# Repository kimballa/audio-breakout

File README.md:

Breadboard audio breakout
=========================

This board is intended to sit next to a pair of breadboards and plug into the power bus rows and the
first few columns of each breadboard. Measurements were taken on Adafruit breadboards.

Power
-----

Power bus rows are filled with +12V, GND, and -12V from the onboard power header.
* This takes a molex 3-pin MicroFit 3.0 cable from a GS-101-PWR.
* There is a power switch, and LEDs to show you when it's engaged.
* There are jumper headers that the power flows through before accessing your board.
  * Close these with SPC02SYAN shunt jumpers to let the power flow.
  * Or hook your ammeter here to measure current consumption precisely.
  * The onboard opamp and LEDs are upstream of the jumpers and will not be included 
    in your current measurements.
* There is also a 3-pin MicroFit 3.0 header to daisy-chain a cable to a module under test,
  for current measurement purposes.

Leveling feet
-------------

The two mounting holes on the outboard edge of the PCB are sized for an M3 screw. A 20mm machine
screw with an integral end-stop like JLCPCB Mechatronics' EKLF-W-P12-M3-L20 can be used to balance
this edge of the board so that it lies flat when you adjust potentiometers or plug in cables.

Reference voltages
-------------------

There are two reference voltages generated onboard and brought out to pins, at 8.0V and 6.0V. Use
the two trimpots on the bottom of the PCB to calibrate these.

Jacks
-----

There are six jacks, `IO1..IO4`, `OUT1`, and `OUT2`. 

The I/O jacks are general purpose and bidirectional. Shields are attached to GND via 1M resistance.
The tip goes to the labeled pin on the breadboard.

OUT1 and OUT2 are unity buffered by an opamp with 220kOhm input impedence. These are intended to
drive a signal to a speaker or other external system. The TL074H opamp is specified to deliver at
least 25mA before losing voltage fidelity. The shields for OUT1 and OUT2 are directly connected to
GND. 

There are also header pins on the top of the board for accessing OUT1 and OUT2 on a 'scope or
multimeter.

Pots
----

There are four PTV09 potentiometers, two at 100kOhm and two at 10kOhm resistance. All three pins of
each pot are brought out to the breadboard. Pin numbers are indicated with one to three dots.

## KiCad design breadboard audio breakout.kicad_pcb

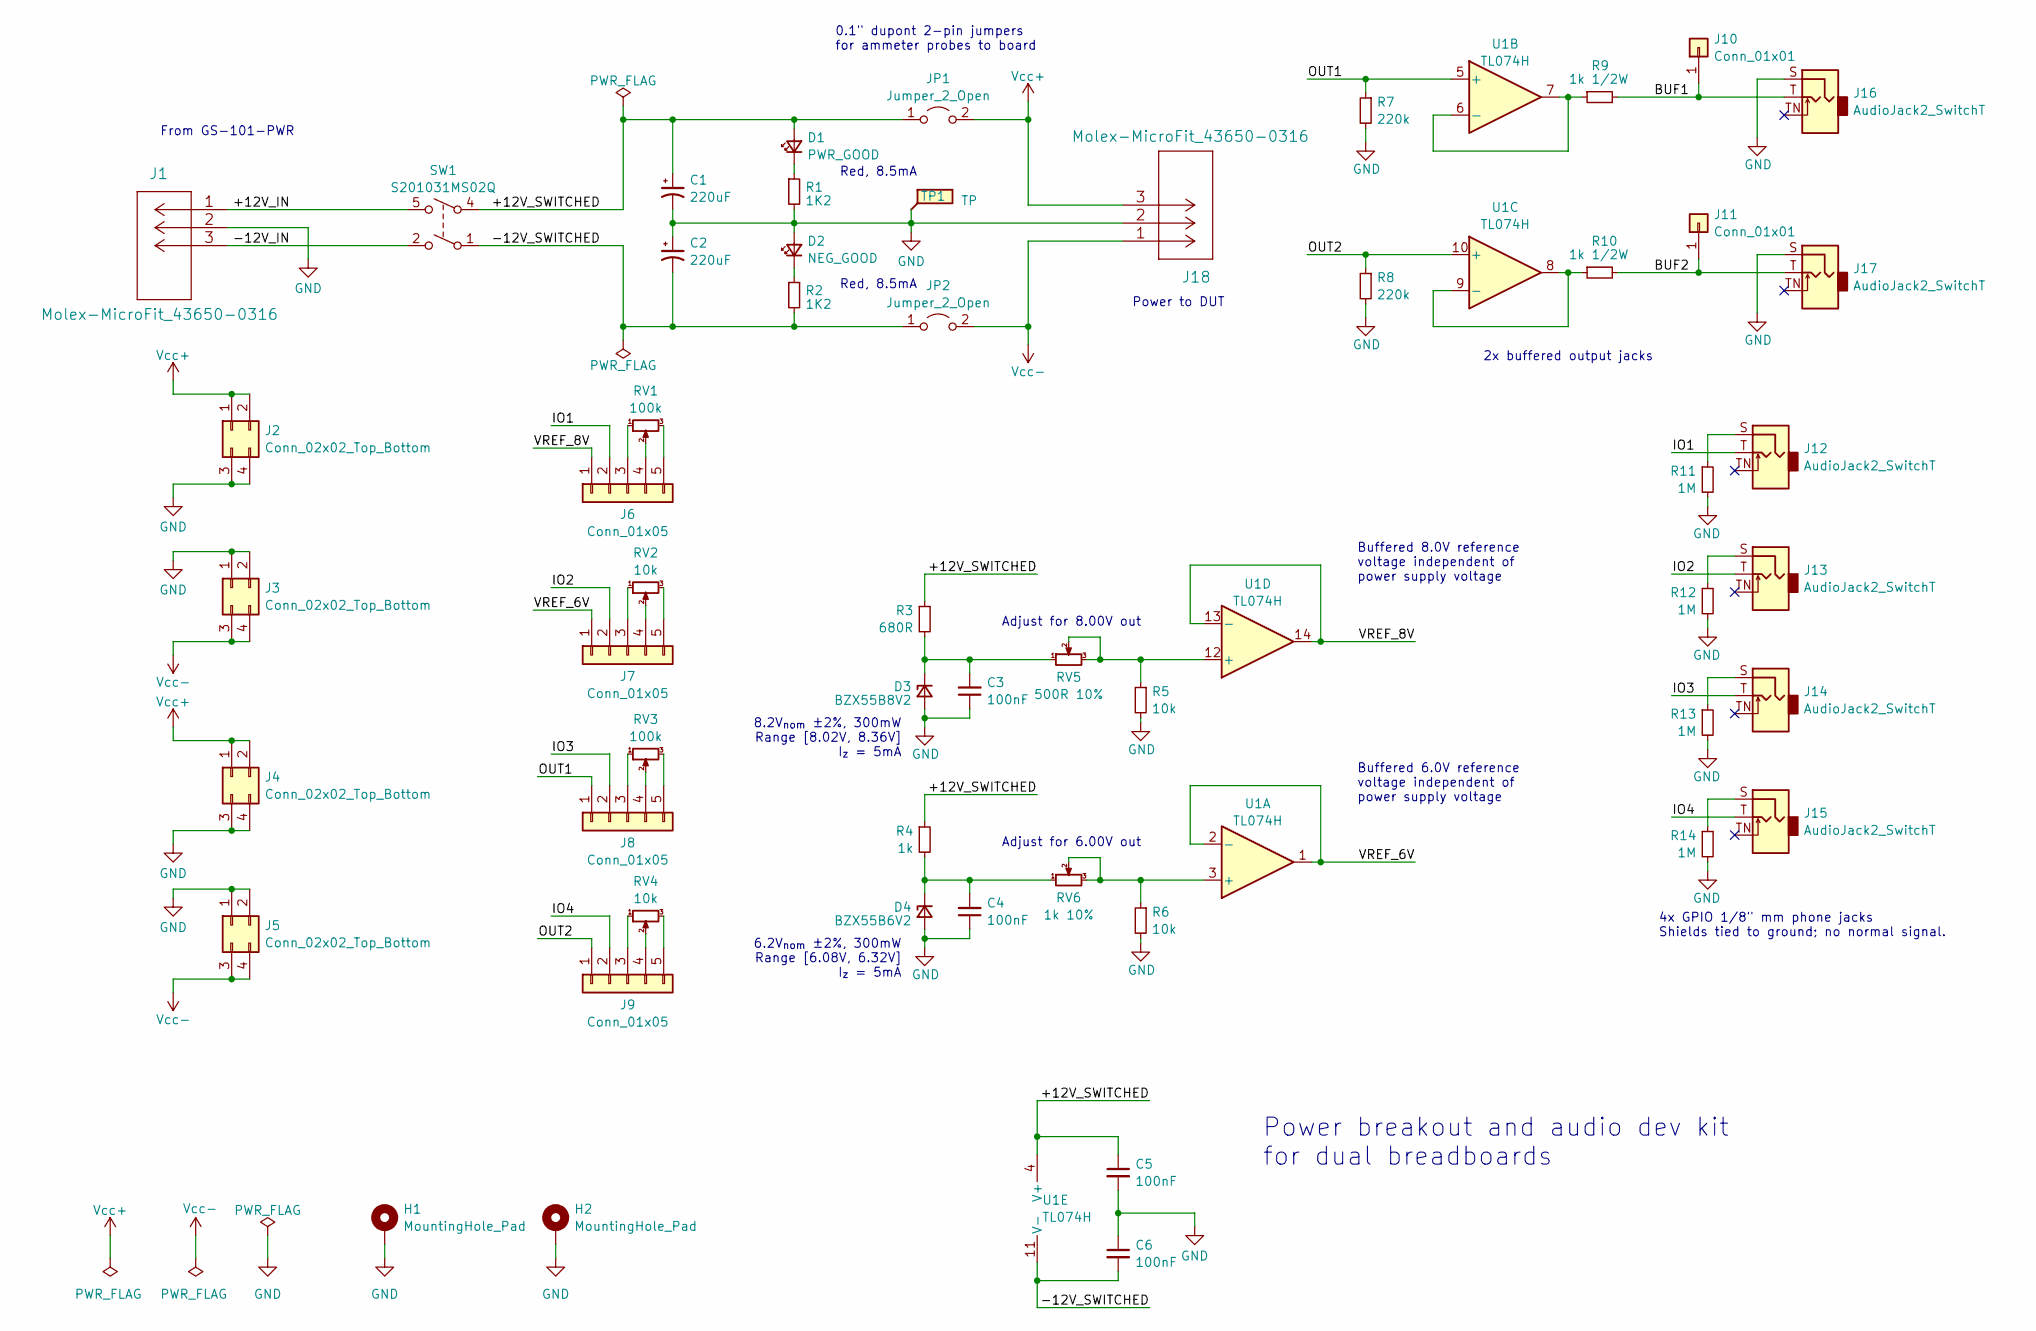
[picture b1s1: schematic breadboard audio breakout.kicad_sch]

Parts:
C1, C2: 220uF; CP_Radial_D10.0mm_P5.00mm; MPN ESW227M035AH9AA
C3, C4, C5, C6: 100nF; C_0805_2012Metric_Pad1.18x1.45mm_HandSolder; MPN CL21B104KBFNNNE
D1: PWR_GOOD; LED_D5.0mm_SilkFix; MPN LTL-4223
D2: NEG_GOOD; LED_D5.0mm_SilkFix; MPN LTL-4223
D3: BZX55B8V2; D_SOD-323_HandSoldering; MPN MM3Z8V2ST1G
D4: BZX55B6V2; D_SOD-323_HandSoldering; MPN MM3Z6V2ST1G
H1, H2: MountingHole_Pad; MountingHole_3.3mm_M3_Full_Standoff_Size
J1, J18: Molex-MicroFit_43650-0316; Molex-Microfit-43650-0316; MPN 436500316
J2, J3, J4, J5: Conn_02x02_Top_Bottom; PinHeader_2x02_P2.54mm_Vertical; MPN 67997-400HLF
J6, J7, J8, J9: Conn_01x05; PinHeader_1x05_P2.54mm_Vertical; MPN 5-146850-1
J10, J11: Conn_01x01; PinHeader_1x01_P2.54mm_Vertical; MPN 5-146850-1
J12, J13, J14, J15, J16, J17: AudioJack2_SwitchT; Schurter-4832.2211; MPN 4832.2211
JP1, JP2: Jumper_2_Open; PinHeader_1x02_P2.54mm_Vertical; MPN 5-146850-1
R1, R2: 1K2; R_0805_2012Metric_Pad1.20x1.40mm_HandSolder; MPN RMCF0805FT1K20
R3: 680R; R_0805_2012Metric_Pad1.20x1.40mm_HandSolder; MPN RMCF0805FT680R
R4: 1k; R_0805_2012Metric_Pad1.20x1.40mm_HandSolder; MPN RMCF0805FT1K00
R5, R6: 10k; R_0805_2012Metric_Pad1.20x1.40mm_HandSolder; MPN RMCF0805FT10K0
R7, R8: 220k; R_0805_2012Metric_Pad1.20x1.40mm_HandSolder; MPN RMCF0805FT220K
R9, R10: 1k 1/2W; R_1206_3216Metric_Pad1.30x1.75mm_HandSolder; MPN RNCP1206FTD1K00
R11, R12, R13, R14: 1M; R_0805_2012Metric_Pad1.20x1.40mm_HandSolder; MPN RMCF0805FT1M00
RV1, RV3: 100k; Pot_Bourns_PTV09_vert_3dModel; MPN PTV09A-4025F-B104
RV2, RV4: 10k; Pot_Bourns_PTV09_vert_3dModel; MPN PTV09A-4025F-B103
RV5: 500R 10%; Pot_Bourns_3362P; MPN 3362P-1-501LF
RV6: 1k 10%; Pot_Bourns_3362P; MPN 3362P-1-102LF
SW1: S201031MS02Q; CK_SPDT_S201031MS02Q; MPN S201031MS02Q
TP1: TP; TP_HeaderPin_P2.54mm_round
U1: TL074H; TI_SOIC_D_R-PDSO-G14; MPN TL074HIDR

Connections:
/+12V_IN: J1.1, SW1.5
/+12V_SWITCHED: C1.1, C5.1, D1.2 (A), JP1.1 (A), R3.1, R4.1, SW1.4, U1.4 (V+)
/-12V_IN: J1.3, SW1.2
/-12V_SWITCHED: C2.2, C6.2, JP2.1 (A), R2.2, SW1.1, U1.11 (V-)
/BUF1: J10.1, J16.T, R9.2
/BUF2: J11.1, J17.T, R10.2
/IO1: J6.2, J12.T
/IO2: J7.2, J13.T
/IO3: J8.2, J14.T
/IO4: J9.2, J15.T
/OUT1: J8.1, R7.1, U1.5 (+)
/OUT2: J9.1, R8.1, U1.10 (+)
/VREF_6V: J7.1, U1.1, U1.2 (-)
/VREF_8V: J6.1, U1.13 (-), U1.14
GND: C1.2, C2.1, C3.1, C4.1, C5.2, C6.1, D2.2 (A), D3.2 (A), D4.2 (A), H1.1, H2.1, J1.2, J2.3, J2.4, J3.1, J3.2, J4.3, J4.4, J5.1, J5.2, J16.S, J17.S, J18.2, R1.2, R5.2, R6.2, R7.2, R8.2, R11.2, R12.2, R13.2, R14.2, TP1.1
unnamed: D1.1 (K), R1.1
unnamed: D2.1 (K), R2.1
unnamed: C3.2, D3.1 (K), R3.2, RV5.1
unnamed: C4.2, D4.1 (K), R4.2, RV6.1
unnamed: J6.3, RV1.1
unnamed: J6.4, RV1.2
unnamed: J6.5, RV1.3
unnamed: J7.3, RV2.1
unnamed: J7.4, RV2.2
unnamed: J7.5, RV2.3
unnamed: J8.3, RV3.1
unnamed: J8.4, RV3.2
unnamed: J8.5, RV3.3
unnamed: J9.3, RV4.1
unnamed: J9.4, RV4.2
unnamed: J9.5, RV4.3
unnamed: J12.S, R11.1
unnamed: J13.S, R12.1
unnamed: J14.S, R13.1
unnamed: J15.S, R14.1
unnamed: R6.1, RV6.2, RV6.3, U1.3 (+)
unnamed: R9.1, U1.6 (-), U1.7
unnamed: R10.1, U1.8, U1.9 (-)
unnamed: R5.1, RV5.2, RV5.3, U1.12 (+)
Vcc+: J2.1, J2.2, J4.1, J4.2, J18.3, JP1.2 (B)
Vcc-: J3.3, J3.4, J5.3, J5.4, J18.1, JP2.2 (B)

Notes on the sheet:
8.2V_{nom} ±2%, 300mW Range [8.02V, 8.36V] I_{z} = 5mA
0.1" dupont 2-pin jumpers for ammeter probes to board
Buffered 8.0V reference voltage independent of power supply voltage
6.2V_{nom} ±2%, 300mW Range [6.08V, 6.32V] I_{z} = 5mA
Adjust for 6.00V out
Red, 8.5mA
Power breakout and audio dev kit for dual breadboards
2x buffered output jacks
From GS-101-PWR
Buffered 6.0V reference voltage independent of power supply voltage
4x GPIO 1/8" mm phone jacks Shields tied to ground; no normal signal.
Power to DUT
Adjust for 8.00V out

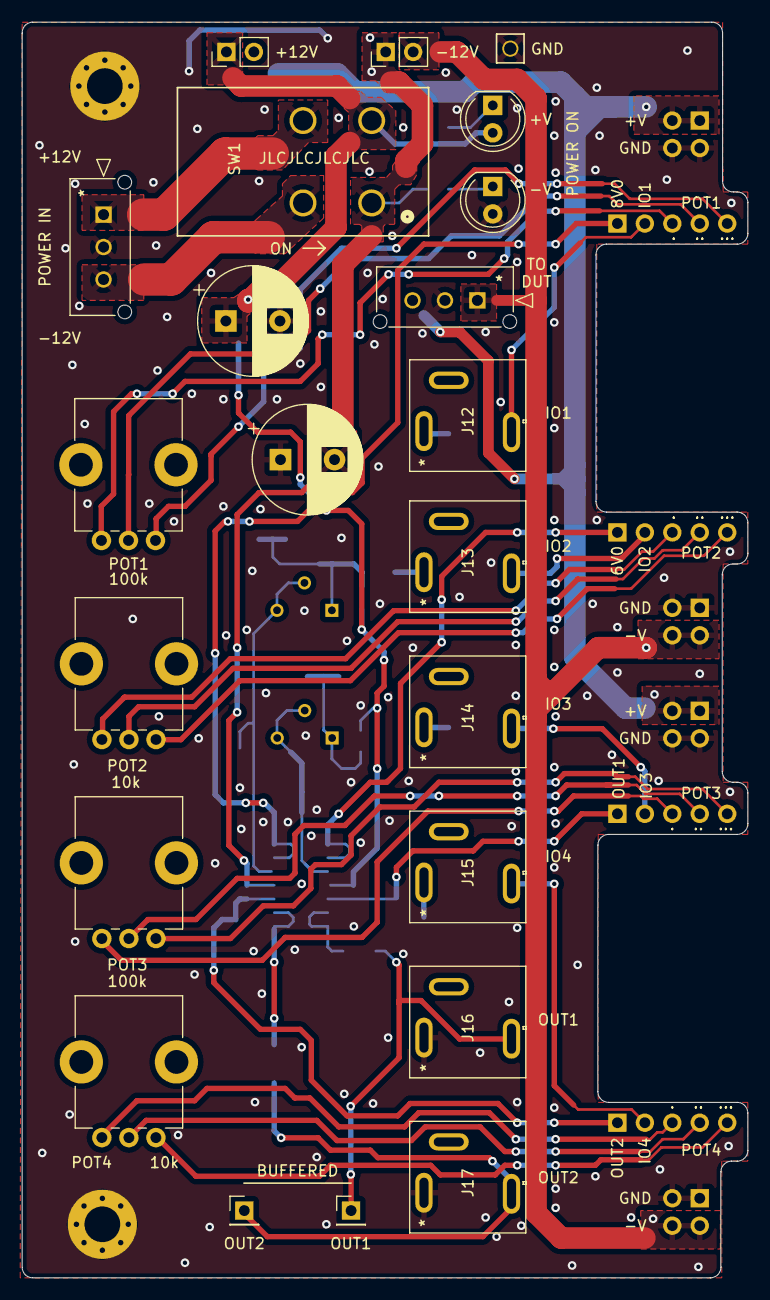
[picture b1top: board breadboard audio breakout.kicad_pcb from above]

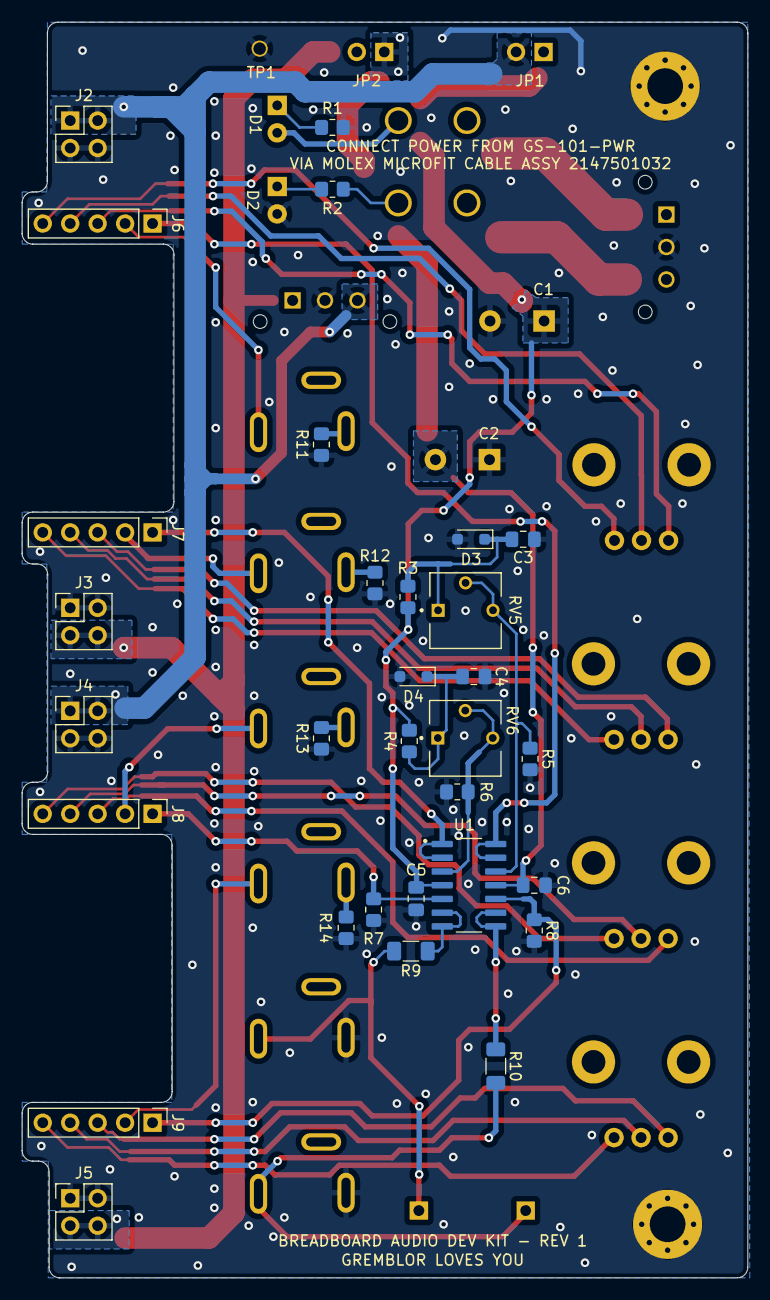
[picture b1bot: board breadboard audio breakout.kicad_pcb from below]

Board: 2 copper layers, 67.1 x 116.2 mm, 55 parts (31 on the bottom side), 41 nets.

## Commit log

2023-12-29 Add gitignore file.
2023-12-29 Add README.
2023-12-29 Add project files.
2023-12-29 Update PCB file with gerber generation config.
2023-12-29 Add v1.0 RTM gerbers.
2024-09-07 Update to KiCad 8.0 format.
2024-12-21 Add license file.
